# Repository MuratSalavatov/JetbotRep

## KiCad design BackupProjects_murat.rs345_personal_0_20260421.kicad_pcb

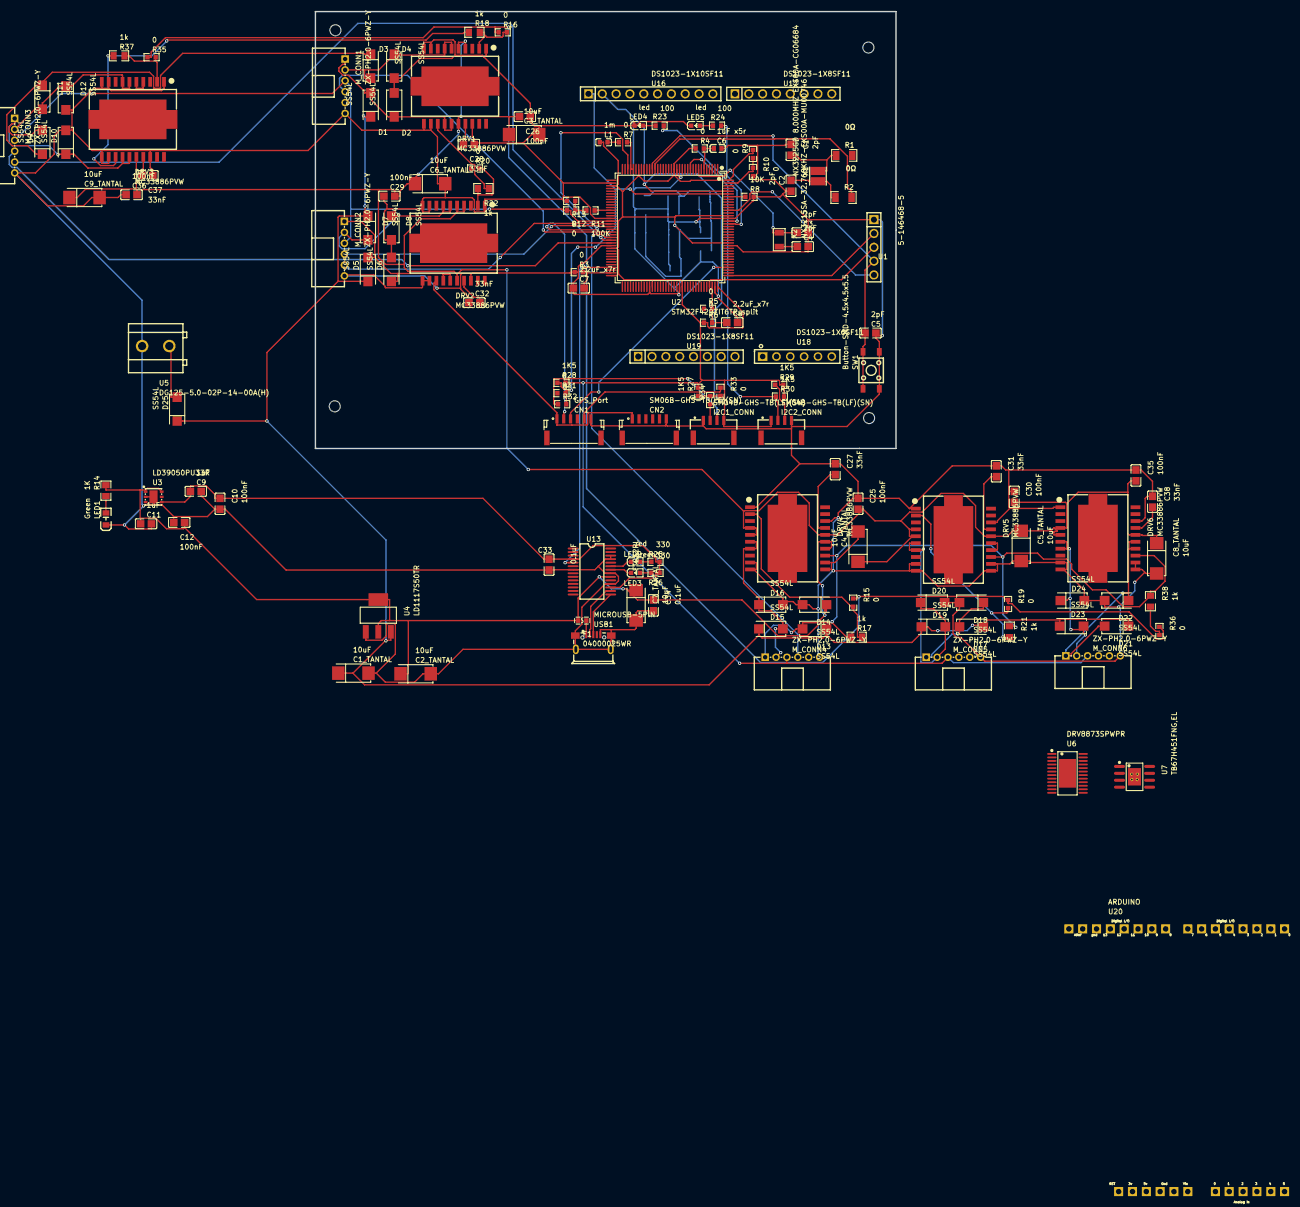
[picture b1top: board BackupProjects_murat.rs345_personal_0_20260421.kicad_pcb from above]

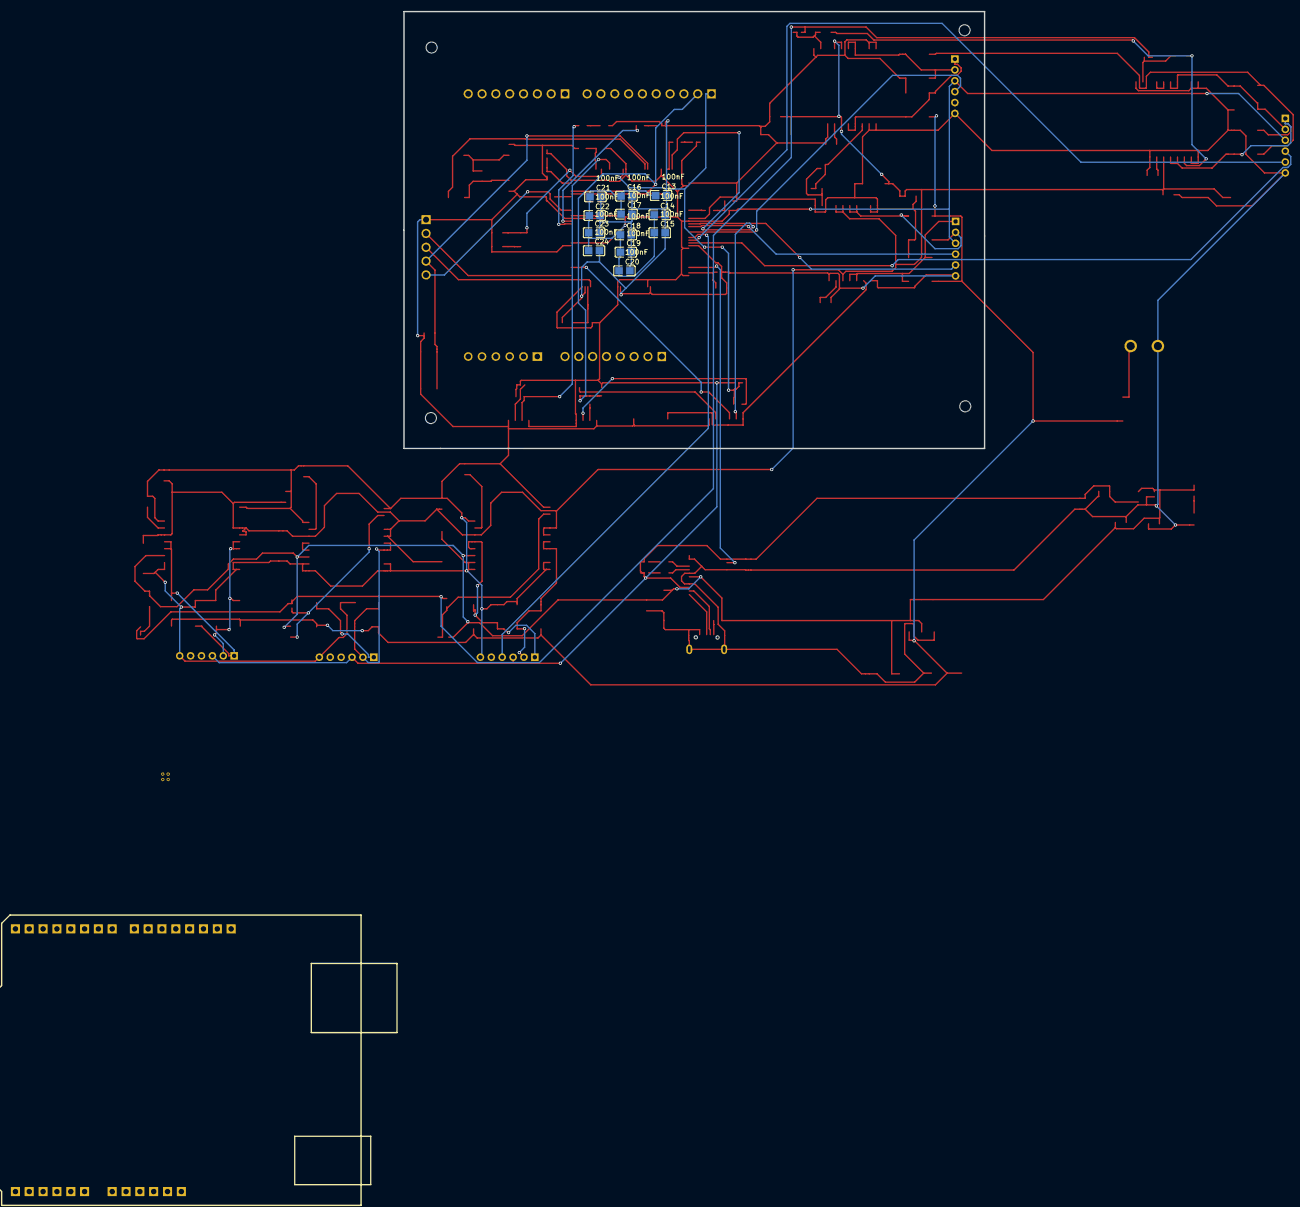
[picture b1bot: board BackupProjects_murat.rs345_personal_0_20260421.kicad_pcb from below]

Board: 2 copper layers, 154 parts (12 on the bottom side), 88 nets.

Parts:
C1, C2, C3, C4, C5: 2pF; C0805
C1_TANTAL, C2_TANTAL, C3_TANTAL, C4_TANTAL, C5_TANTAL, C6_TANTAL, C7_TANTAL, C8_TANTAL, C9_TANTAL: 10uF; CAP-SMD_L6.0-W3.2-FD-A
C6: 1uF x5r; C0603
C7, C8: 2.2uF_x7r; C0805
C9, C11: 1uF; C0805
C10, C12, C13, C14, C15, C16, C17, C18, C19, C20, C21, C22, C23, C24, C25, C26, C29, C30, C35, C36: 100nF; C0805
C27, C28, C31, C32, C37, C38: 33nF; C0805
C33, C34: 0.1uF; C0805
CN1: GPS_Port; CONN-TH_SM06B-GHS-TB-LF-SN
CN2: SM06B-GHS-TB(LF)(SN); CONN-TH_SM06B-GHS-TB-LF-SN
D1, D2, D3, D4, D5, D6, D7, D8, D9, D10, D11, D12, D13, D14, D15, D16, D17, D18, D19, D20, D21, D22, D23, D24, D25: SS54L; SMA_L4.4-W2.6-LS5.0-RD
DRV1, DRV2, DRV3, DRV4, DRV5, DRV6: MC33886PVW; HSOP-20_L15.9-W11.0-P1.27-LS14.2-BL-EP
F1: 04000025WR; F0603
Hole_gge640689: Hole_gge640689
Hole_gge640704: Hole_gge640704
Hole_gge640719: Hole_gge640719
Hole_gge640734: Hole_gge640734
I2C1_CONN, I2C2_CONN: SM04B-GHS-TB(LF)(SN); CONN-SMD_4P-P1.25_SM04B-GHS-TB-LF-SN
L1: 1m; L0603
LED1: Green; LED0805-RD
LED2: red; LED0603-RD
LED3: green; LED0603-RD
LED4, LED5: led; LED0603-RD
M_CONN1, M_CONN2, M_CONN3, M_CONN4, M_CONN5, M_CONN6: ZX-PH2.0-6PWZ-Y; CONN-TH_6P-P2.00_ZX-PH2.0-6PWZ-Y
R1, R2: 0Ω; R1206
R3, R4, R5, R6, R7, R9, R10, R12, R13, R15, R16, R19, R20, R31, R32, R33, R34, R35, R36: 0; R0603
R8: 10K; R0603
R11: 100K; R0603
R14: 1K; R0805
R17, R18, R21, R22, R37, R38: 1k; R0805
R23, R24: 100; R0603
R25, R26: 330; R0603
R27, R28, R29, R30: 1K5; R0603
SW1: Button-SMD-4.5x4.5x5.5; SW-SMD_4P-L4.5-W4.5-P3.00-LS7.0
U1: 5-146468-5; HDR-TH_5P-P2.54-V-M
U2: STM32F429ZIT6TR_split; LQFP-144_L20.0-W20.0-P0.50-LS22.0-BL
U3: LD39050PU33R; DFN-6_L3.0-W3.0-P0.95-LS3.1-TL-EP
U4: LD1117S50TR; SOT-223-3_L6.5-W3.4-P2.30-LS7.0-BR
U5: DG125-5.0-02P-14-00A(H); CONN-TH_DG125-5.0-02P-14-00A
U6: DRV8873SPWPR; HTSSOP-24_L7.8-W4.4-P0.65-LS6.4-TL-EP
U7: TB67H451FNG,EL; HSOP-8_L5.0-W4.0-P1.27-LS6.2-BL-EP
U13: FT232RL; SSOP-28_L10.2-W5.3-P0.65-LS7.8-BL
U16: DS1023-1X10SF11; HDR-TH_10P-P2.54-V-F
U17, U19: DS1023-1X8SF11; HDR-TH_8P-P2.54-V-F
U18: DS1023-1X6SF11; HDR-TH_6P-P2.54-V-F
U20: ARDUINO; ARDUINO-BPLACE
USB1: MICROUSB-5PIN; USB-SMD_5P_MICROUSB-5PIN
X1: NX3225GD 8.000MHZ EXS00A-CG06684; CRYSTAL-SMD_2P-L3.2-W2.5
X2: NX3215SA-32.768KHZ-EXS00A-MU00746; CRYSTAL-SMD_L3.2-W1.5-1

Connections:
+5V: C2_TANTAL.1, C7_TANTAL.1, C11.1, C12.1, C34.1, CN1.1, CN2.1, DRV1.13, DRV2.13, DRV3.13, DRV4.13, DRV5.13, DRV6.13, F1.2, R14.2, R17.1, R18.1, R21.1, R22.1, R37.1, R38.1, U3.1, U3.6, U4.2, U4.4, U13.20, U19.5
AVDD: R7.2, U2.32, U2.33, U16.3
BOOT0: R8.1, U2.138
BOOT1: R11.1, U2.48
C31_2: C31.2, DRV5.17
C37_2: C37.2, DRV3.17
CN1_4: CN1.4, R31.1
CN1_5: CN1.5, R33.1
CONN_M1_1: D3.2, D4.1, DRV1.6, DRV1.7, M_CONN1.2
CONN_M1_2: D1.2, D2.1, DRV1.14, DRV1.15, M_CONN1.1
CONN_M2_1: D7.2, D8.1, DRV2.6, DRV2.7, M_CONN2.2
CONN_M2_2: D5.2, D6.1, DRV2.14, DRV2.15, M_CONN2.1
CONN_M3_1: D11.2, D12.1, DRV3.6, DRV3.7, M_CONN3.2
CONN_M3_2: D9.2, D10.1, DRV3.14, DRV3.15, M_CONN3.1
CONN_M4_1: D15.2, D16.1, DRV4.6, DRV4.7, M_CONN4.2
CONN_M4_2: D13.2, D14.1, DRV4.14, DRV4.15, M_CONN4.1
CONN_M5_1: D19.2, D20.1, DRV5.6, DRV5.7, M_CONN5.2
CONN_M5_2: D17.2, D18.1, DRV5.14, DRV5.15, M_CONN5.1
DRV1_2: DRV1.2, R16.2, R18.2
DRV1_17: C28.2, DRV1.17
DRV2_2: DRV2.2, R20.2, R22.2
DRV2_17: C32.2, DRV2.17
DRV4_2: DRV4.2, R15.2, R17.2
DRV4_17: C27.2, DRV4.17
DRV6_2: DRV6.2, R36.2, R38.2
DRV6_17: C38.2, DRV6.17
ENC_A_M1: M_CONN1.5, U2.55
ENC_A_M2: M_CONN2.5, U2.53
ENC_A_M3: M_CONN3.5, U2.59
ENC_A_M4: M_CONN4.5, U2.57
ENC_B_M1: M_CONN1.4, U2.56
ENC_B_M2: M_CONN2.4, U2.54
ENC_B_M3: M_CONN3.4, U2.60
ENC_B_M4: M_CONN4.4, U2.58
EXT_RXD: U2.69, U13.5
EXT_TXD: U2.78, U13.1
FS1: R15.1, R16.1, R19.1, R20.1, R35.1, R36.1
GND: C1.1, C1_TANTAL.2, C2.1, C2_TANTAL.2, C3.2, C3_TANTAL.2, C4.2, C4_TANTAL.2, C5.2, C5_TANTAL.2, C6.2, C6_TANTAL.2, C7.1, C7_TANTAL.2, C8.2, C8_TANTAL.2, C9.2, C9_TANTAL.2, C10.2, C11.2, C12.2, C13.2, C14.2, C15.2, C16.2, C17.2, C18.2, C19.2, C20.2, C21.2, C22.2, C23.2, C24.2, C25.1, C26.1, C27.1, C28.1, C29.1, C30.1, C31.1, C32.1, C33.2, C34.2, C35.1, C36.1, C37.1, C38.1, CN1.6, CN2.6, D2.2, D4.2, D6.2, D8.2, D10.2, D12.2, D14.2, D16.2, D18.2, D20.2, D22.2, D24.2, DRV1.1, DRV1.9, DRV1.10, DRV1.11, DRV1.12, DRV1.18, DRV2.1, DRV2.9, DRV2.10, DRV2.11, DRV2.12, DRV2.18, DRV3.1, DRV3.9, DRV3.10, DRV3.11, DRV3.12, DRV3.18, DRV4.1, DRV4.9, DRV4.10, DRV4.11, DRV4.12, DRV4.18, DRV5.1, DRV5.9, DRV5.10, DRV5.11, DRV5.12, DRV5.18, DRV6.1, DRV6.9, DRV6.10, DRV6.11, DRV6.12, DRV6.18, I2C1_CONN.1, I2C2_CONN.4, LED1.1, LED4.1, LED5.1, M_CONN1.6, M_CONN2.6, M_CONN3.6, M_CONN4.6, M_CONN5.6, M_CONN6.6, R3.1, R8.2, R10.2, R13.2, SW1.3, SW1.4, U1.1, U2.16, U2.38, U2.51, U2.61, U2.83, U2.94, U2.107, U2.120, U2.130, U3.2, U3.7, U4.1, U5.2, U13.7, U13.18, U13.21, U13.25, U13.26, U16.4, U19.6, U19.7, USB1.5, USB1.6, USB1.7, USB1.8, USB1.9
I2C1_CONN_2: I2C1_CONN.2, R34.1
I2C1_CONN_3: I2C1_CONN.3, R32.1
I2C2_SCL: I2C2_CONN.2, R30.1, U2.11
I2C2_SDA: I2C2_CONN.3, R29.1, U2.10
I2C_SCL: R28.1, R31.2, R32.2, U2.139, U16.1
I2C_SDA: R27.1, R33.2, R34.2, U2.140, U16.2
L1_2: L1.2, R7.1
LED1_2: LED1.2, R14.1
LED2_1: LED2.1, U13.23
LED3_1: LED3.1, U13.22
M6_1: D23.2, D24.1, DRV6.6, DRV6.7, M_CONN6.2
M6_2: D21.2, D22.1, DRV6.14, DRV6.15, M_CONN6.1
NRST: C5.1, SW1.1, SW1.2, U1.4, U2.25, U19.3
PA3(A0): U2.37, U18.1
PC0(A1): U2.26, U18.2
PC3(A2): U2.29, U18.3
PF3(A3): U2.13, U18.4
PF5(A4): U2.15, U18.5
PF10(A5): U2.22, U18.6
PG13: R24.2, U2.128
PG14: R23.2, U2.129
R11_2: R11.2, R12.1, R13.1
R19_2: DRV5.2, R19.2, R21.2
R23_1: LED4.2, R23.1
R24_1: LED5.2, R24.1
R25_1: LED2.2, R25.1
R26_1: LED3.2, R26.1
R35_2: DRV3.2, R35.2, R37.2
SWO: U1.5, U2.133
TCK: U1.2, U2.109
TMS: U1.3, U2.105
U2_23: R1.2, U2.23
U2_24: R2.2, U2.24
U2_71: C7.2, R3.2, U2.71
U2_106: C8.1, R5.2, R6.2, U2.106
U2_143: R9.1, R10.1, U2.143
U5_1: D25.2, U5.1
USART4_RX: CN1.3, U2.112
USART4_TX: CN1.2, U2.34
USB1_1: F1.1, USB1.1
USBDM: U13.16, USB1.2
USBDP: U13.15, USB1.3
VBAT: C6.1, R4.2, U2.6
VCC: C3_TANTAL.1, C4_TANTAL.1, C5_TANTAL.1, C6_TANTAL.1, C8_TANTAL.1, C9_TANTAL.1, C25.2, C26.2, C29.2, C30.2, C35.2, C36.2, DRV1.4, DRV1.5, DRV1.16, DRV2.4, DRV2.5, DRV2.16, DRV3.4, DRV3.5, DRV3.16, DRV4.4, DRV4.5, DRV4.16, DRV5.4, DRV5.5, DRV5.16, DRV6.4, DRV6.5, DRV6.16
VDD: C9.1, C10.1, C13.1, C14.1, C15.1, C16.1, C17.1, C18.1, C19.1, C20.1, C21.1, C22.1, C23.1, C24.1, C33.1, I2C1_CONN.4, I2C2_CONN.1, L1.1, M_CONN1.3, M_CONN2.3, M_CONN3.3, M_CONN4.3, M_CONN5.3, M_CONN6.3, R4.1, R6.1, R9.2, R12.2, R25.2, R26.2, R27.2, R28.2, R29.2, R30.2, U2.17, U2.30, U2.39, U2.52, U2.62, U2.72, U2.84, U2.95, U2.108, U2.121, U2.131, U2.144, U3.4, U13.4, U13.17, U19.4
VIN: C1_TANTAL.1, D1.1, D3.1, D5.1, D7.1, D9.1, D11.1, D13.1, D15.1, D17.1, D19.1, D21.1, D23.1, D25.1, U4.3, U19.8
X1_1: C1.2, R1.1, X1.1
X1_2: C2.2, R2.1, X1.2
X2_1: C3.1, U2.8, X2.1
X2_2: C4.1, U2.9, X2.2
